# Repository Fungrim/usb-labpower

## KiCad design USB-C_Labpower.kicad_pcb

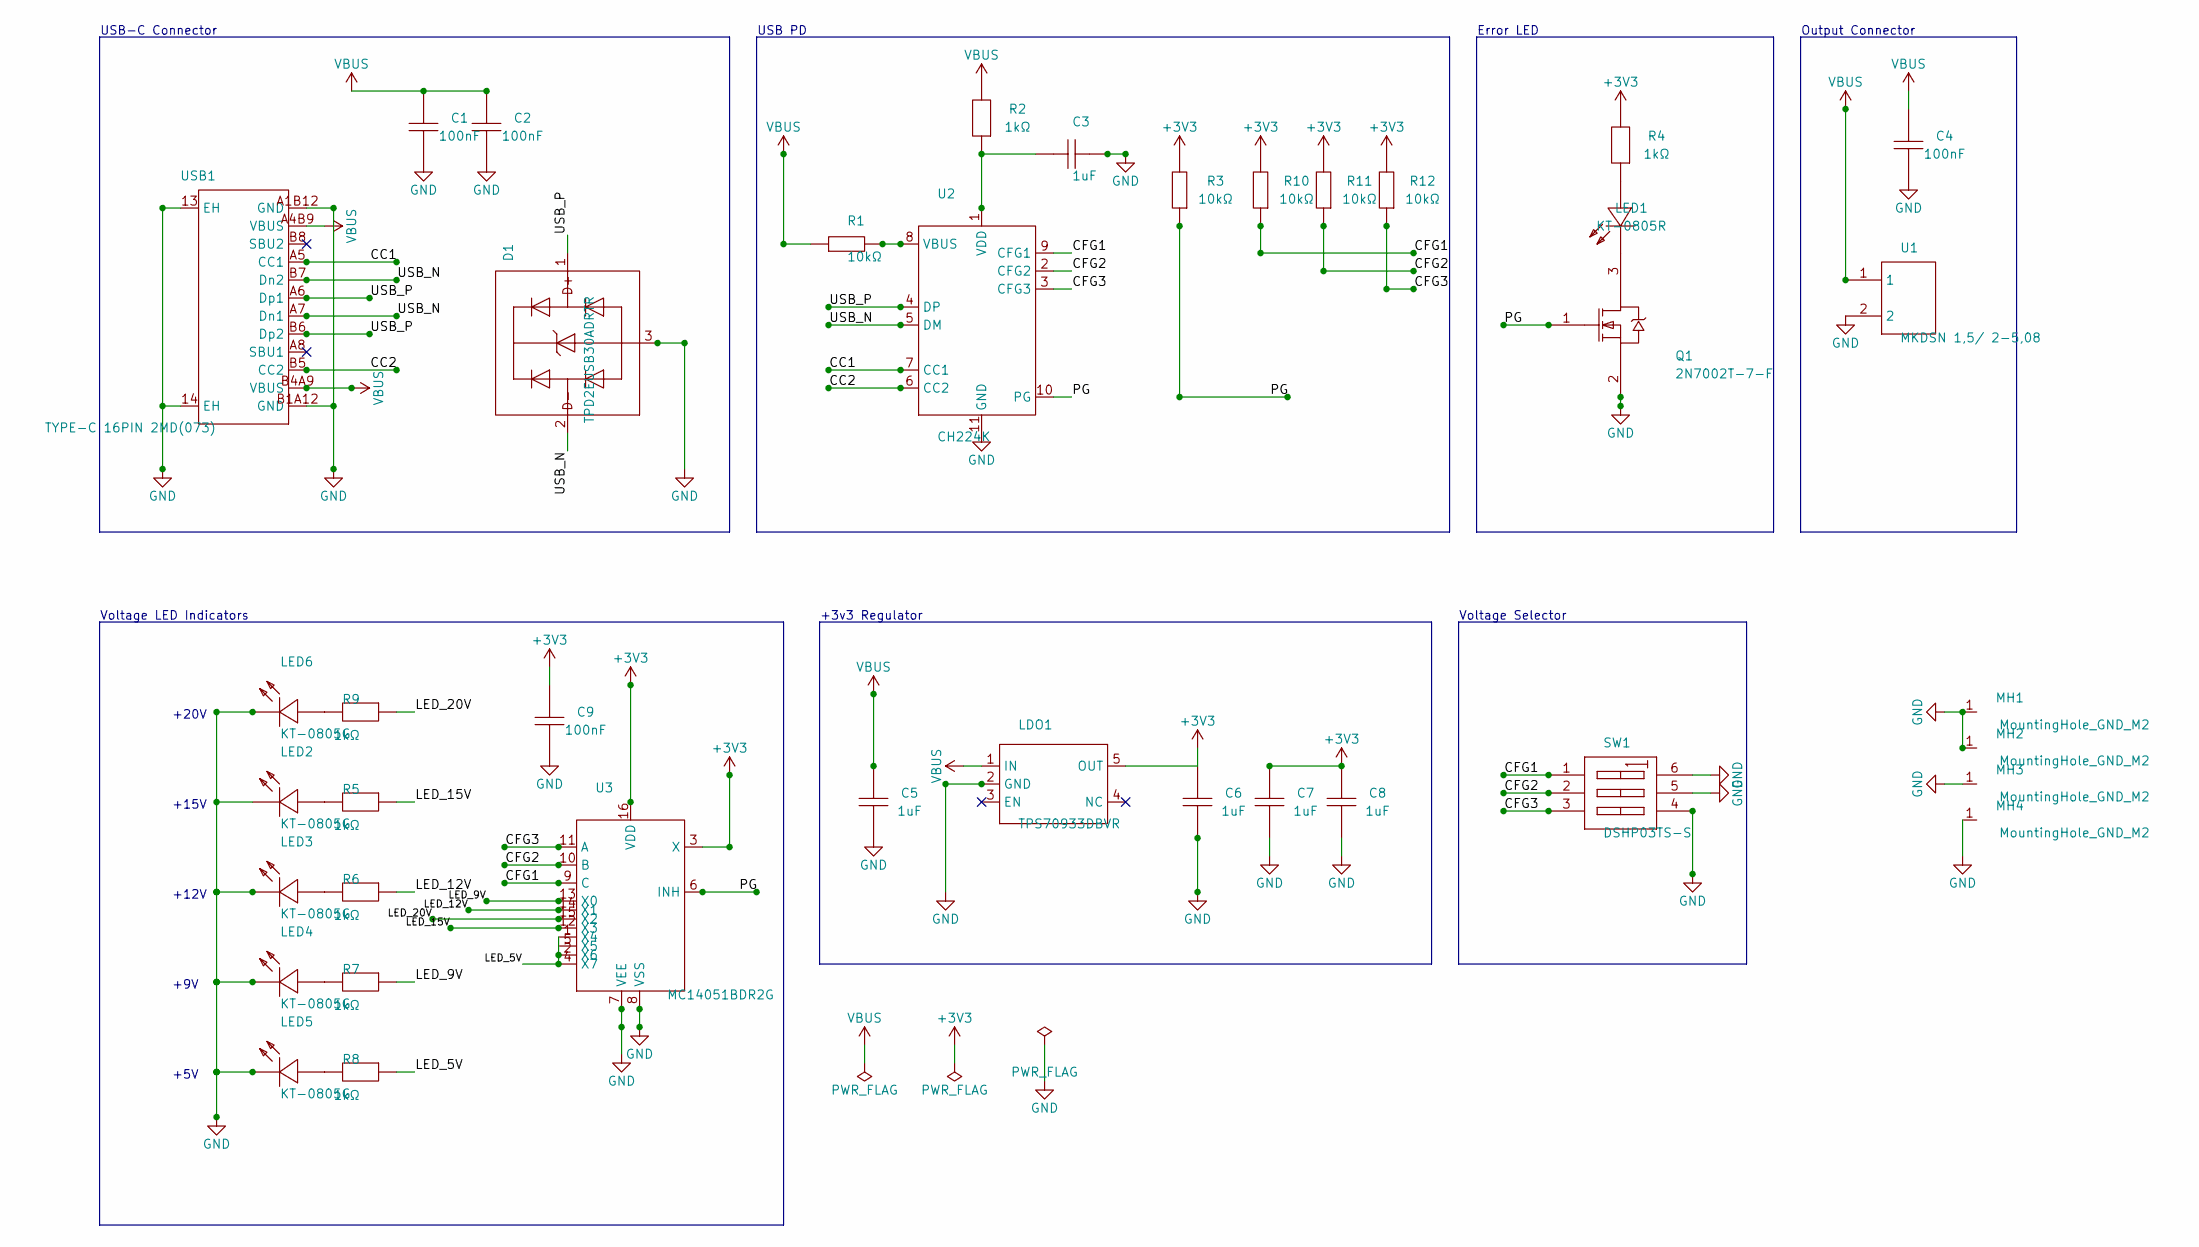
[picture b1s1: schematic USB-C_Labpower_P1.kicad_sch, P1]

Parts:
C1, C2, C4, C9: 100nF; C0402_fe13d333b50dbdf69fdd0b1c72ae60195ff71708283c3ace39e97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
C3, C5, C6, C7, C8: 1uF; C0603_e7558fb3b29d58abcf24614c732acbd04bb36be132957fffd4a68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
D1: TPD2EUSB30ADRTR; SOT-9X3-3_L1_0-W0_8-P0_35-LS1_0-BR_2c7aeb55600744d54da2287f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
LDO1: TPS70933DBVR; SOT-23-5_L3_0-W1_7-P0_95-LS2_8-BR_1901982714f82598d2a911a4a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
LED1: KT-0805R; LED0805-R-RD_aa15e764cecd16930063835b2dfe9f1773561f0e7e9d8c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
LED2, LED3, LED4, LED5, LED6: KT-0805G; LED0805-R-RD_aa15e764cecd16930063835b2dfe9f1773561f0e7e9d8c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
MH1, MH2, MH3, MH4: MountingHole_GND_M2; MountingHole_GND_M2_63d95bc1cb9821d9c709497a4a4595c174d9974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
Q1: 2N7002T-7-F; SOT-523-3_L1_6-W0_8-P1_00-LS1_6-BR_3c30ff8cd59f582ed319f4d9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
R1, R3, R10, R11, R12: 10kΩ; R0402_a86f5b5d3e21c2acd84f6a857da2cf8fa61d0ee72e35986ffd16a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
R2, R4, R5, R6, R7, R8, R9: 1kΩ; R0402_a86f5b5d3e21c2acd84f6a857da2cf8fa61d0ee72e35986ffd16a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
SW1: DSHP03TS-S; SW-SMD_DSHP03TS-S_466340ffa1d3d04f672f8cef72bb4ed74a7a0bea2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
U1: MKDSN 1,5/ 2-5,08; CONN-TH_2P-P5_08_1729128_bae87082d1b914e0b4f97facced3f7eba8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
U2: CH224K; ESSOP-10_L4_9-W3_9-P1_0-LS6_0-TL-EP_fa7f2b2a6050bc52d8447fa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
U3: MC14051BDR2G; SOIC-16_L9_9-W3_9-P1_27-LS6_0-BL_db09d5edbc1fea359cbaf6488f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
USB1: TYPE-C 16PIN 2MD(073); USB-C-SMD_TYPE-C-16PIN-2MD-073_ee93bb81cc34824a99a494037f3e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

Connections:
+3V3: C6.1, C7.1, C8.1, C9.2, LDO1.5 (OUT), R3.2, R4.2, R10.2, R11.2, R12.2, U3.3 (X), U3.16 (VDD)
/P1/CC1: U2.7 (CC1), USB1.A5 (CC1)
/P1/CC2: U2.6 (CC2), USB1.B5 (CC2)
/P1/CFG1: R10.1, SW1.1, U2.9 (CFG1), U3.9 (C)
/P1/CFG2: R11.1, SW1.2, U2.2 (CFG2), U3.10 (B)
/P1/CFG3: R12.1, SW1.3, U2.3 (CFG3), U3.11 (A)
/P1/LED_5V: R8.1, U3.1 (X4), U3.2 (X6), U3.4 (X7), U3.5 (X5)
/P1/LED_9V: R7.1, U3.13 (X0)
/P1/LED_12V: R6.1, U3.14 (X1)
/P1/LED_15V: R5.1, U3.12 (X3)
/P1/LED_20V: R9.1, U3.15 (X2)
/P1/PG: Q1.1 (G), R3.1, U2.10 (PG), U3.6 (INH)
/P1/USB_N: D1.2 (D-), U2.5 (DM), USB1.A7 (Dn1), USB1.B7 (Dn2)
/P1/USB_P: D1.1 (D+), U2.4 (DP), USB1.A6 (Dp1), USB1.B6 (Dp2)
GND: C1.1, C2.1, C3.1, C4.1, C5.2, C6.2, C7.2, C8.2, C9.1, D1.3 (GND), LDO1.2 (GND), LED2.2 (K), LED3.2 (K), LED4.2 (K), LED5.2 (K), LED6.2 (K), MH1.1, MH2.1, MH3.1, MH4.1, Q1.2 (S), SW1.4, SW1.5, SW1.6, U1.2, U2.11 (GND), U3.7 (VEE), U3.8 (VSS), USB1.13 (EH), USB1.14 (EH), USB1.A1B12 (GND), USB1.B1A12 (GND)
unnamed: LED1.1 (A), R4.1
unnamed: LED1.2 (K), Q1.3 (D)
unnamed: LED2.1 (A), R5.2
unnamed: LED3.1 (A), R6.2
unnamed: LED4.1 (A), R7.2
unnamed: LED5.1 (A), R8.2
unnamed: LED6.1 (A), R9.2
unnamed: R1.2, U2.8 (VBUS)
unnamed: C3.2, R2.1, U2.1 (VDD)
VBUS: C1.2, C2.2, C4.2, C5.1, LDO1.1 (IN), R1.1, R2.2, U1.1, USB1.A4B9 (VBUS), USB1.B4A9 (VBUS)

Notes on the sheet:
Voltage Selector
Voltage LED Indicators
+9V
Error LED
+12V
+5V
USB PD
Output Connector
+15V
USB-C Connector
+3v3 Regulator
+20V

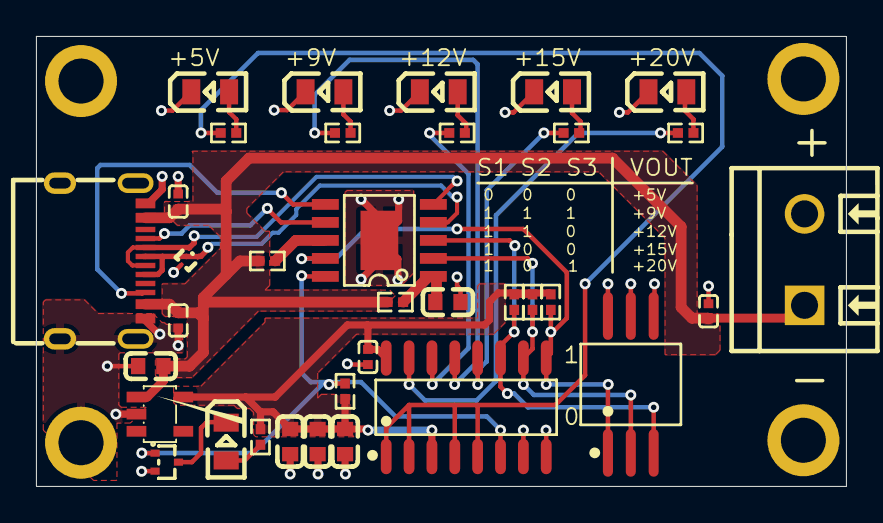
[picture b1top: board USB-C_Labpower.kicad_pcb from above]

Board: 4 copper layers, 45.0 x 25.0 mm, 39 parts (0 on the bottom side), 25 nets.
